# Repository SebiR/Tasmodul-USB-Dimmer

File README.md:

# Tasmodul USB-Dimmer
A plug-in dimmer for USB powered lamps and lights to be used with Tasmota, WLED or custom ESP8266 firmwares.

## Features
* Small formfactor (21x42mm without USB)
* Up to 2A output current (approx.)
* 2 buttons for user interfacing

## Configuration
* GPIO4: Inverted PWM output (or switch)
* GPIO5: Inverted push button "DOWN"
* GPIO13: Inverted push button "UP"
* GPIO0: Inverted LED indicator

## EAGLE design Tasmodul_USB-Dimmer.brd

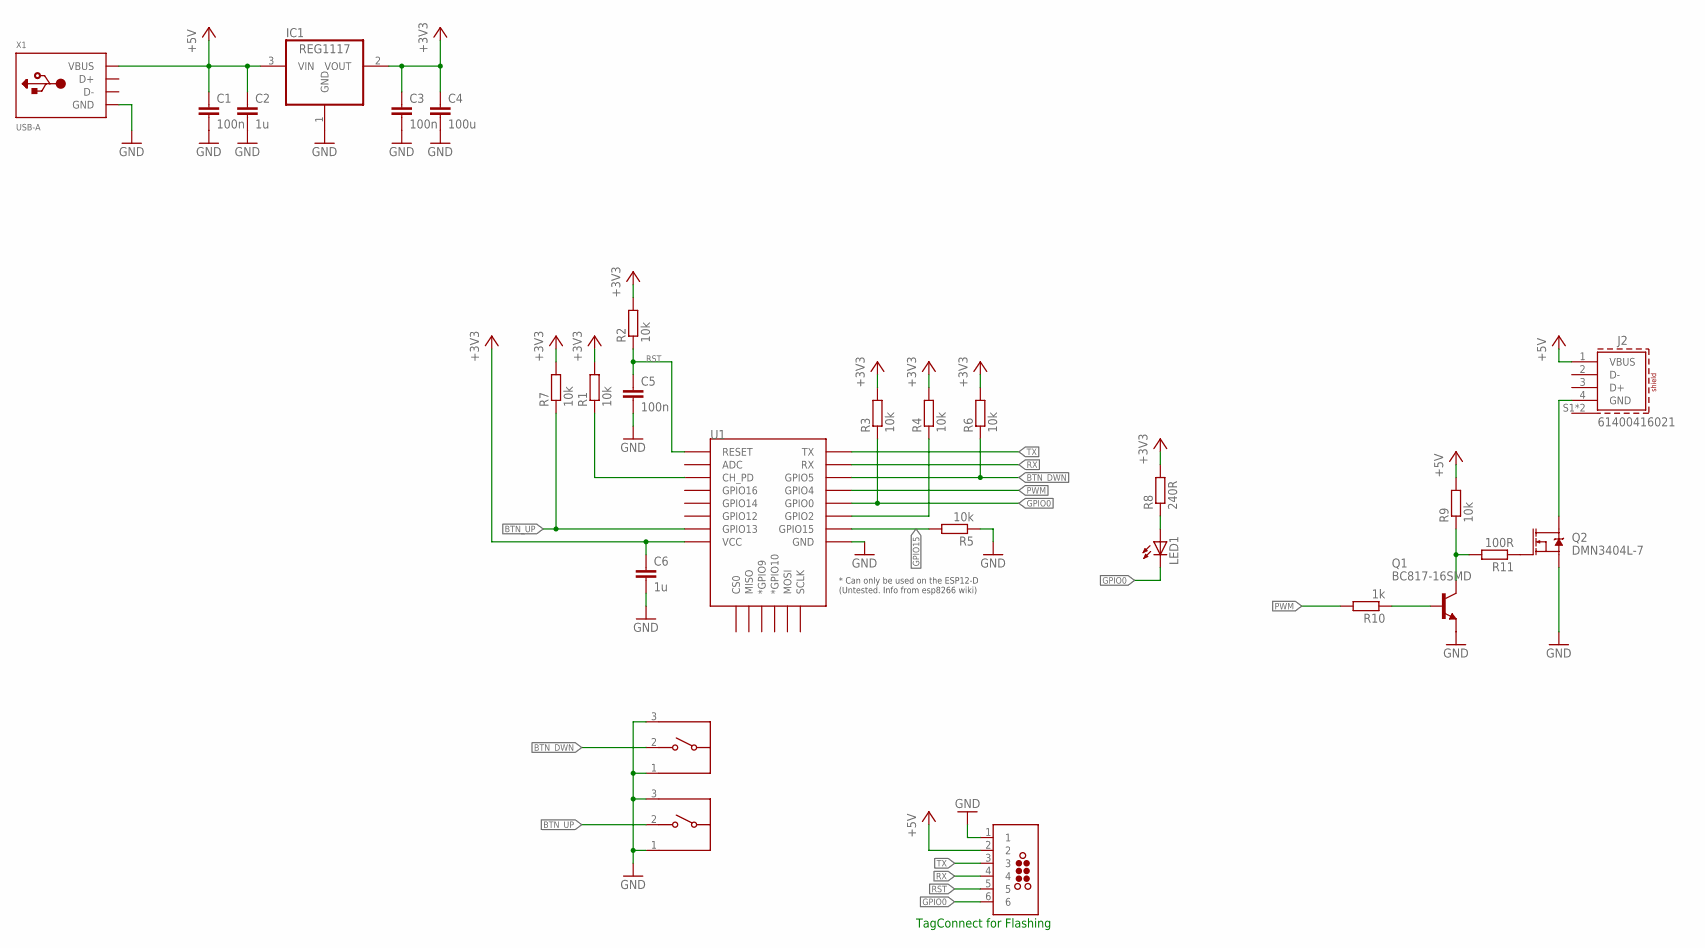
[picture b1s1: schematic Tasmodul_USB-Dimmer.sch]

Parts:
C1, C3, C5: 100n; C0603
C2, C6: 1u; C0603
C4: 100u; C0603
IC1: REG1117; SOT223
J2: 61400416021
J6: TC2030-MCP-NL
LED1: LEDCHIP-LED0603; CHIP-LED0603
Q1: BC817-16SMD; SOT23-BEC
Q2: DMN3404L-7; SOT23-3
R1, R2, R3, R4, R5, R6, R7, R9: 10k; R0603
R8: 240R; R0603
R10: 1k; R0603
R11: 100R; R0603
S1, S2: 436333033816
U1: ESP12ESMD; ESP12E-SMD
X1: USB-A; MOLEX_480371000

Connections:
+3V3: C3.1, C4.1, C6.1, IC1.2 (VOUT), R1.2, R2.2, R3.2, R4.2, R6.2, R7.2, R8.2, U1.VCC
+5V: C1.1, C2.1, IC1.3 (VIN), J2.1 (VBUS), J6.2, R9.2, X1.1 (VBUS)
BTN_DWN: R6.1, S2.2, U1.GPIO5
BTN_UP: R7.1, S1.2, U1.GPIO13
GND: C1.2, C2.2, C3.2, C4.2, C5.2, C6.2, IC1.1 (GND), J6.1, Q1.E, Q2.2 (S), R5.1, S1.1, S1.3, S2.1, S2.3, U1.GND, X1.4 (GND)
GPIO0: J6.6, LED1.C, R3.1, U1.GPIO0
GPIO15: R5.2, U1.GPIO15
unnamed: LED1.A, R8.1
unnamed: Q2.1 (G), R11.1
unnamed: Q1.B, R10.1
unnamed: R1.1, U1.CH_PD
unnamed: R4.1, U1.GPIO2
unnamed: Q1.C, R9.1, R11.2
unnamed: J2.4 (GND), Q2.3 (D)
PWM: R10.2, U1.GPIO4
RST: C5.1, J6.5, R2.1, U1.RESET
RX: J6.4, U1.RXD0 (RX)
TX: J6.3, U1.TXD0 (TX)

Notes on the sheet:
TagConnect for Flashing

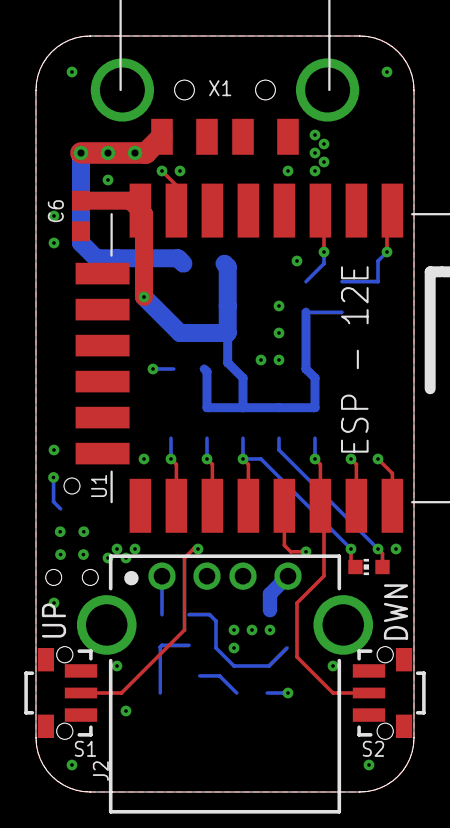
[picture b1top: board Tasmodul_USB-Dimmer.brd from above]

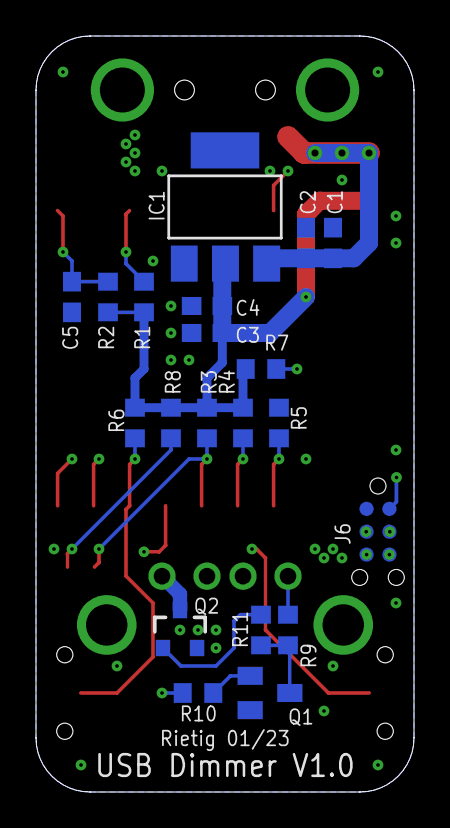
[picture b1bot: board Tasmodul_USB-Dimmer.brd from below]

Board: 4 copper layers, 21.0 x 42.0 mm, 27 parts (20 on the bottom side), 18 nets.

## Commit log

2023-03-02 Cleaned up schematic Added SCH and GERBER Updated documentation

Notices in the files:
parts and their libraries:
tag-connect: ©2009 ROFA.cz - modified and updated by Robert Darlington ‹rdarlington@gmail.com›
Wurth_Connectors_WR-USB: Copyright: Würth Elektronik
SparkFun-DiscreteSemi: Licensing: Creative Commons ShareAlike 4.0 International - https://creativecommons.org/licenses/by-sa/4.0
